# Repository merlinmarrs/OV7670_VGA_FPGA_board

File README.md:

# OV7670_VGA_FPGA_board

An iCE40HX4K Lattice FPGA development board which takes OV7670 camera-in at 30 frames per second and outputs 640x480 VGA @ 60Hz at a resolution of 320x120 in black and white. (The image above is a bit misleading, the OV7670 needs to be plugged in at the edge of the board next to the buttons, not in the center of the board)

The board can work stand-alone with a USB-C or it can be plugged-in to an Arduino to more easily change registers on the OV7670.

# Acknowledgements : 

The FPGA board design was inspired by the iCEstick Evaluation Kit and the [Alhambra] (https://alhambrabits.com/alhambra-2/) which was also an inspiration for the VGA output code.
Verilog code for the OV7670 inspired by the FPGA class 6.111 (Introductory Digital Systems Laboratory) [OV7670-Verilog](https://github.com/westonb/OV7670-Verilog). 
The first prototype of this board was supported by the [IFT](https://ift.devinci.fr/).

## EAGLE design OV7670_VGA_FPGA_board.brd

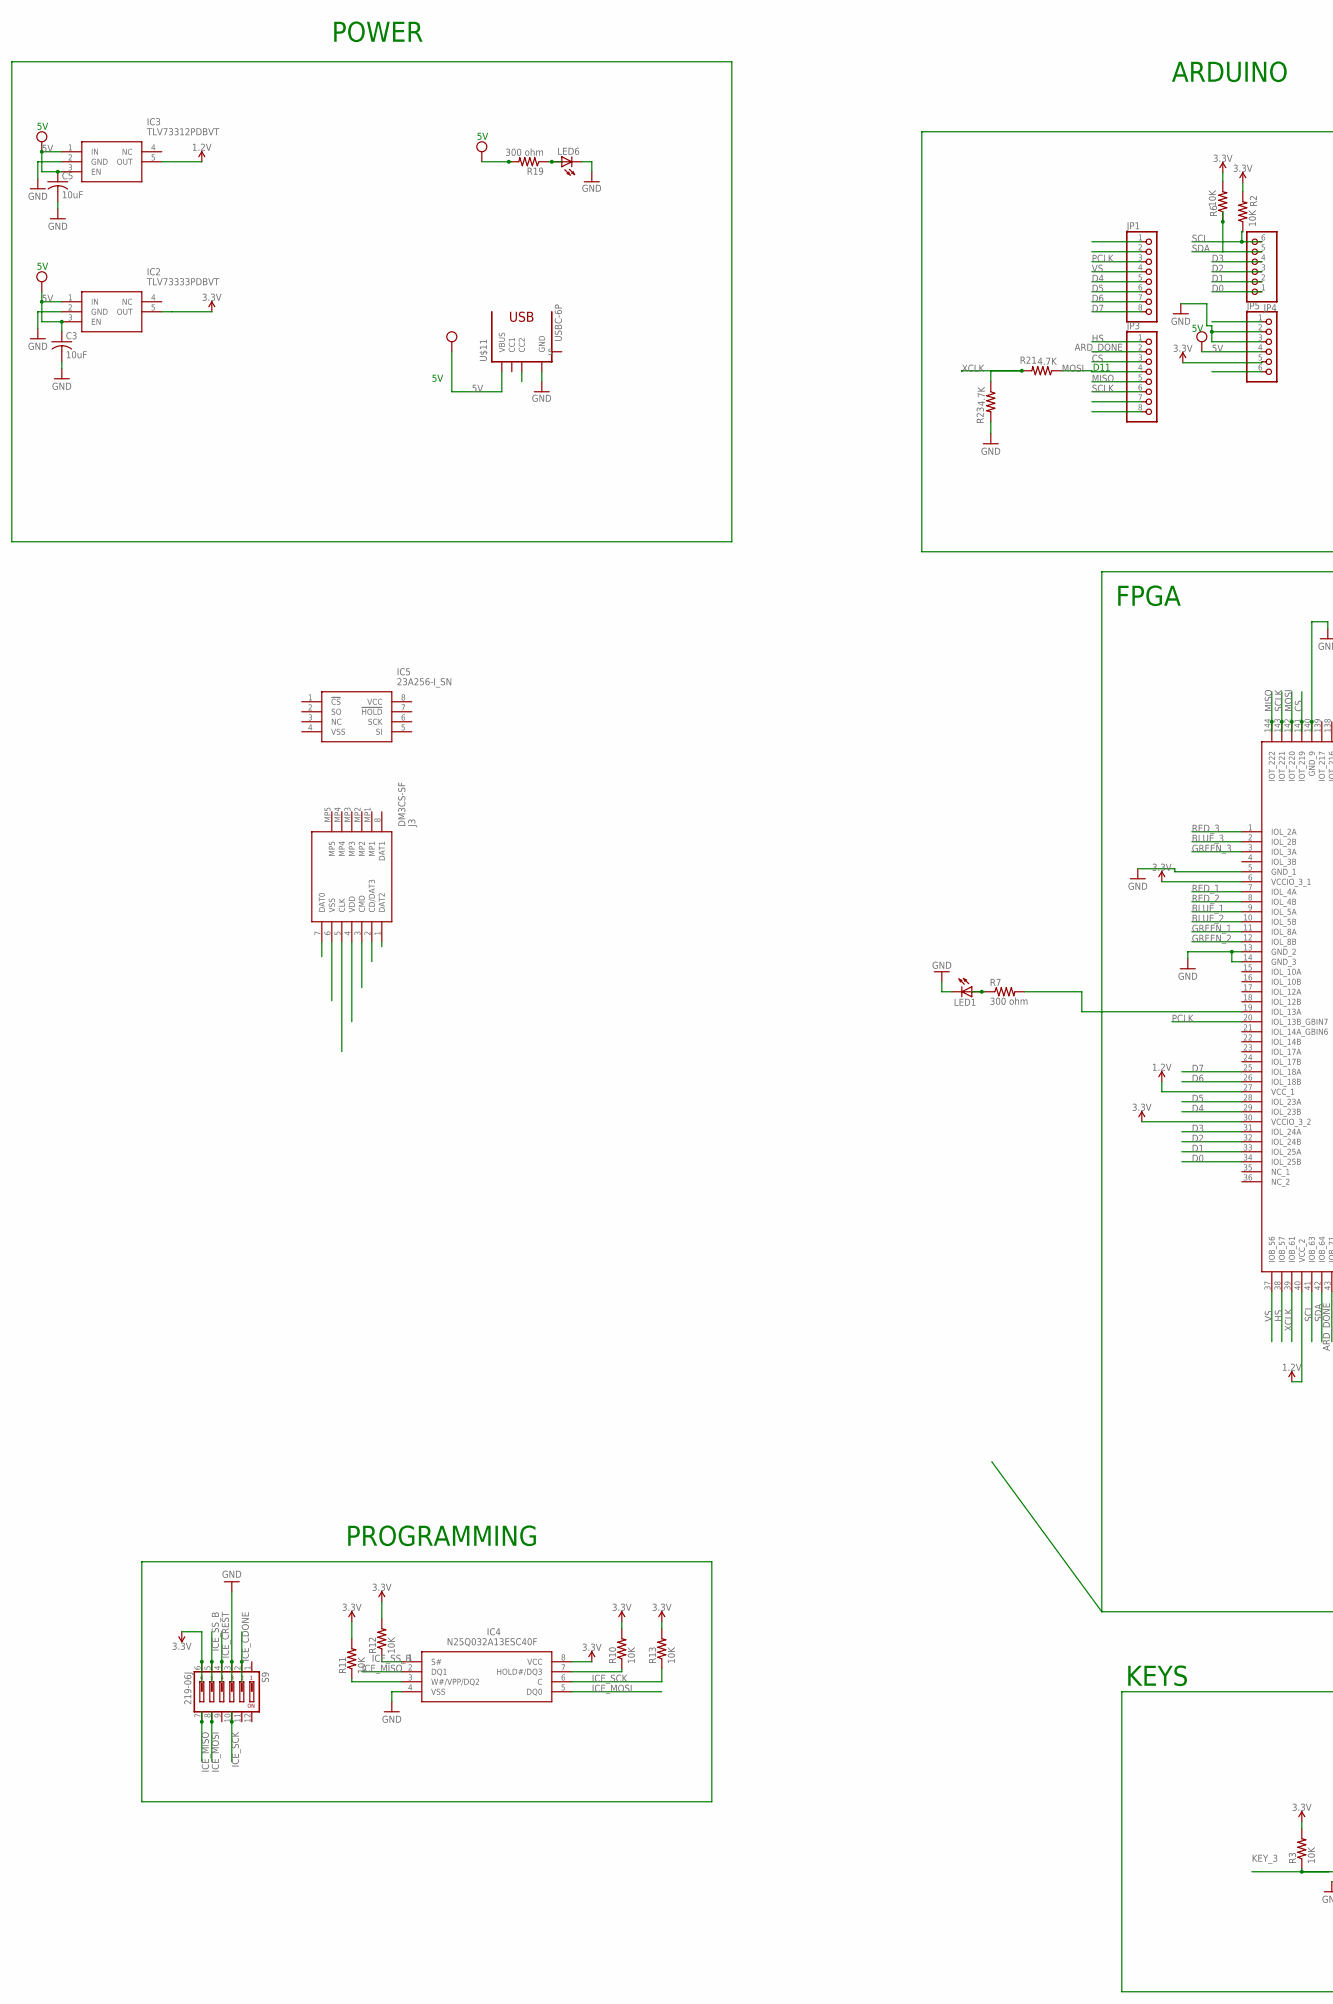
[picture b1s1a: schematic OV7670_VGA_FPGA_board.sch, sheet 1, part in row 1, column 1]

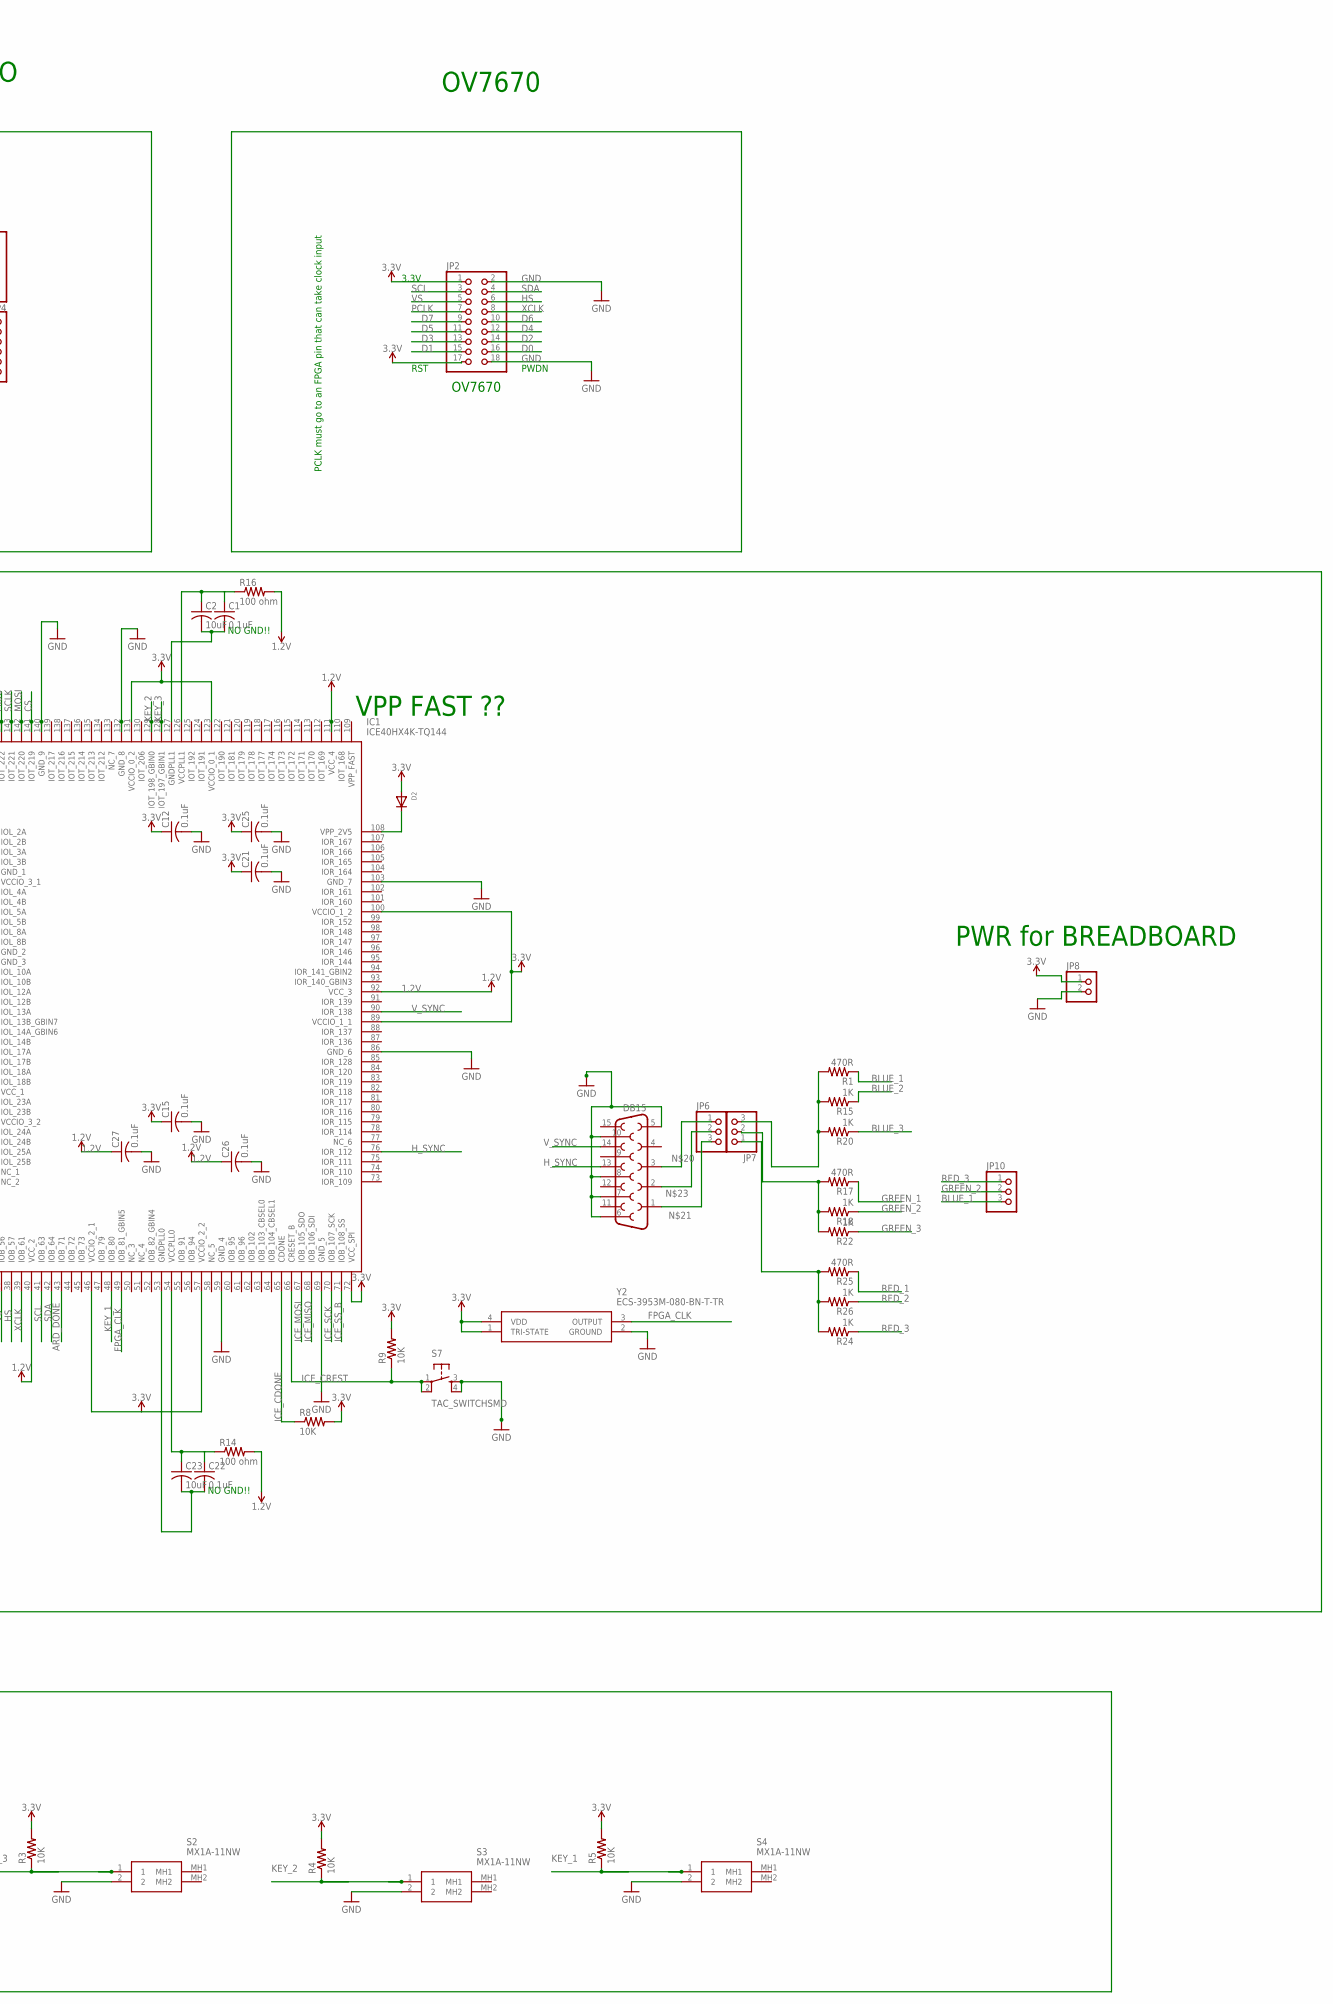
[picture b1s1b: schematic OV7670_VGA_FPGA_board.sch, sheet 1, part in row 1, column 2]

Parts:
C1, C12, C15, C21, C22, C25, C26, C27: 0.1uF; C0805
C2, C3, C5, C23: 10uF; C0805
D2: DIODESOD-323F; SOD-323F
IC1: ICE40HX4K-TQ144; QFP50P2200X2200X160-144N
IC2: TLV73333PDBVT; SOT95P280X145-5N
IC3: TLV73312PDBVT; SOT95P280X145-5N
IC4: N25Q032A13ESC40F; SOIC127P600X175-8N
IC5: 23A256-I_SN; SOIC127P600X175-8N
J3: DM3CS-SF; DM3CSSF
JP1, JP3: PINHD-1X8CLEANBIG; 1X08-CLEANBIG
JP2: PINHD-2X9/90; 2X09/90
JP4, JP5: PINHD-1X6CB; 1X06-CLEANBIG
JP6, JP7, JP10: PINHD-1X3; 1X03
JP8: PINHD-1X2; 1X02
LED1, LED6: LEDCHIPLED_0805; CHIPLED_0805
R1, R17, R25: 470R; R0805
R2, R3, R4, R5, R6, R8, R9, R10, R11, R12, R13: 10K; R0805
R7, R19: 300 ohm; R0805
R14, R16: 100 ohm; R0805
R15, R18, R20, R22, R24, R26: 1K; R0805
R21, R23: 4.7K; R0805
S2, S3, S4: MX1A-11NW; MX1A11NW
S7: TAC_SWITCHSMD; TACTILE-SWITCH-SMD
S9: 219-06J; CTS-219-06J
U$1: DB15
U$11: USBC-6P; USCX-06FX-XXMX-01
Y2: ECS-3953M-080-BN-T-TR; ECS3953M080BNTTR

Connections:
1.2V: C26.1, C27.1, IC1.27 (VCC_1), IC1.40 (VCC_2), IC1.92 (VCC_3), IC1.111 (VCC_4), IC3.5 (OUT), R14.2, R16.2
3.3V: C12.1, C15.1, C21.1, C25.1, D2.A, IC1.6 (VCCIO_3_1), IC1.30 (VCCIO_3_2), IC1.46 (VCCIO_2_1), IC1.57 (VCCIO_2_2), IC1.72 (VCC_SPI), IC1.89 (VCCIO_1_1), IC1.100 (VCCIO_1_2), IC1.123 (VCCIO_0_1), IC1.131 (VCCIO_0_2), IC2.5 (OUT), IC4.8 (VCC), JP2.1, JP2.17, JP5.5, JP8.1, R2.2, R3.2, R4.2, R5.2, R6.2, R8.2, R9.2, R10.2, R11.2, R12.2, R13.2, S9.6, Y2.1 (TRI-STATE), Y2.4 (VDD)
3.3V1: J3.4 (VDD)
5V: C3.1, C5.1, IC2.1 (IN), IC2.3 (EN), IC3.1 (IN), IC3.3 (EN), JP5.4, R19.2, U$11.VBUS1 (VBUS), U$11.VBUS2 (VBUS)
ARD_DONE: IC1.43 (IOB_71), JP3.2
BLUE: JP7.3, R1.2, R15.2, R20.2
BLUE_1: IC1.9 (IOL_5A), JP10.3, R1.1
BLUE_2: IC1.10 (IOL_5B), R15.1
BLUE_3: IC1.2 (IOL_2B), R20.1
CMD: J3.3 (CMD)
CS: IC1.141 (IOT_219), JP3.3
D0: IC1.34 (IOL_25B), JP2.16, JP4.1
D1: IC1.33 (IOL_25A), JP2.15, JP4.2
D2: IC1.32 (IOL_24B), JP2.14, JP4.3
D3: IC1.31 (IOL_24A), JP2.13, JP4.4
D4: IC1.29 (IOL_23B), JP1.5, JP2.12
D5: IC1.28 (IOL_23A), JP1.6, JP2.11
D6: IC1.26 (IOL_18B), JP1.7, JP2.10
D7: IC1.25 (IOL_18A), JP1.8, JP2.9
DAT0: J3.7 (DAT0)
DAT2: J3.1 (DAT2)
DAT3: J3.2 (CD/DAT3)
FPGA_CLK: IC1.49 (IOB_81_GBIN5), Y2.3 (OUTPUT)
GND: C3.2, C5.2, C12.2, C15.2, C21.2, C25.2, C26.2, C27.2, IC1.5 (GND_1), IC1.13 (GND_2), IC1.14 (GND_3), IC1.59 (GND_4), IC1.69 (GND_5), IC1.86 (GND_6), IC1.103 (GND_7), IC1.132 (GND_8), IC1.140 (GND_9), IC2.2 (GND), IC3.2 (GND), IC4.4 (VSS), JP2.2, JP2.18, JP5.2, JP5.3, JP8.2, LED1.C, LED6.C, R23.2, S2.2, S3.2, S4.2, S7.3, S7.4, S9.3, U$1.5, U$1.6, U$1.7, U$1.8, U$1.10, U$11.GND1 (GND), U$11.GND2 (GND), Y2.2 (GROUND)
GND1: J3.6 (VSS)
GREEN: JP7.2, R17.2, R18.2, R22.2
GREEN_1: IC1.11 (IOL_8A), R17.1
GREEN_2: IC1.12 (IOL_8B), JP10.2, R18.1
GREEN_3: IC1.3 (IOL_3A), R22.1
HS: IC1.38 (IOB_57), JP2.6, JP3.1
H_SYNC: IC1.76 (IOR_112), U$1.13
ICE_CDONE: IC1.65 (CDONE), R8.1, S9.2
ICE_CREST: IC1.66 (CRESET_B), R9.1, S7.1, S7.2, S9.4
ICE_MISO: IC1.68 (IOB_106_SDI), IC4.2 (DQ1), S9.7
ICE_MOSI: IC1.67 (IOB_105_SDO), IC4.5 (DQ0), S9.8
ICE_SCK: IC1.70 (IOB_107_SCK), IC4.6 (C), R13.1, S9.10
ICE_SS_B: IC1.71 (IOB_108_SS), IC4.1 (S#), R12.1, S9.5
KEY_1: IC1.48 (IOB_80), R5.1, S4.1
KEY_2: IC1.129 (IOT_198_GBIN0), R4.1, S3.1
KEY_3: IC1.128 (IOT_197_GBIN1), R3.1, S2.1
MISO: IC1.144 (IOT_222), JP3.5
MOSI: IC1.142 (IOT_220), JP3.4, R21.1
unnamed: IC4.7 (HOLD#/DQ3), R10.1
unnamed: LED6.A, R19.1
unnamed: IC4.3 (W#/VPP/DQ2), R11.1
unnamed: C22.1, C23.1, IC1.54 (VCCPLL0), R14.1
unnamed: LED1.A, R7.1
unnamed: IC1.19 (IOL_13A), R7.2
unnamed: D2.C, IC1.108 (VPP_2V5)
unnamed: JP6.1, U$1.3
unnamed: JP6.3, U$1.1
unnamed: C1.1, C2.1, IC1.126 (VCCPLL1), R16.1
unnamed: JP6.2, U$1.2
unnamed: C1.2, C2.2, IC1.127 (GNDPLL1)
unnamed: C22.2, C23.2, IC1.53 (GNDPLL0)
PCLK: IC1.20 (IOL_13B_GBIN7), JP1.3, JP2.7
RED: JP7.1, R24.2, R25.2, R26.2
RED_1: IC1.7 (IOL_4A), R25.1
RED_2: IC1.8 (IOL_4B), R26.1
RED_3: IC1.1 (IOL_2A), JP10.1, R24.1
SCL: IC1.41 (IOB_63), JP2.3, JP4.6, R2.1
SCLK: IC1.143 (IOT_221), JP3.6
SDA: IC1.42 (IOB_64), JP2.4, JP4.5, R6.1
SD_CLK: J3.5 (CLK)
VS: IC1.37 (IOB_56), JP1.4, JP2.5
V_SYNC: IC1.90 (IOR_138), U$1.14
XCLK: IC1.39 (IOB_61), JP2.8, R21.2, R23.1

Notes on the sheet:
NO GND!!
POWER
PROGRAMMING
FPGA
OV7670
ARDUINO
PCLK must go to an FPGA pin that can take clock input
KEYS
RST
D11
PWDN
3.3V
PWR for BREADBOARD
VPP FAST ??

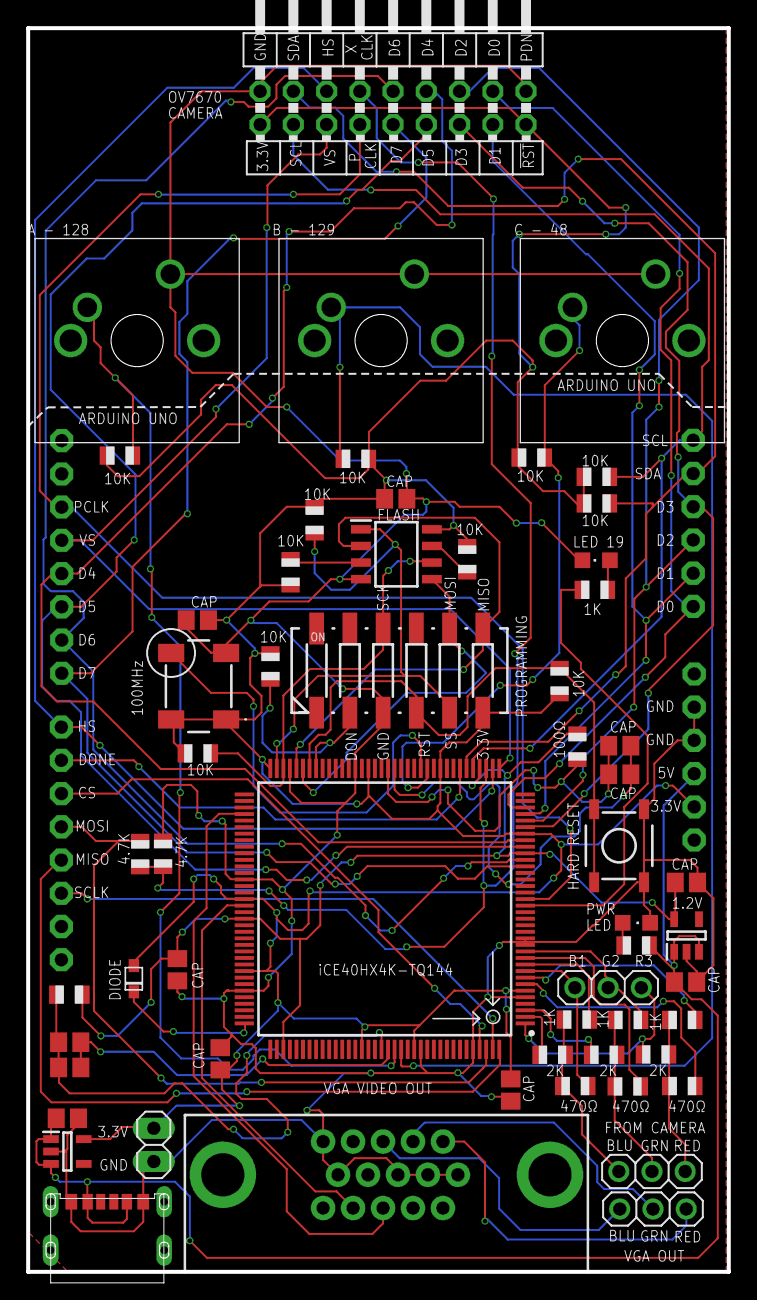
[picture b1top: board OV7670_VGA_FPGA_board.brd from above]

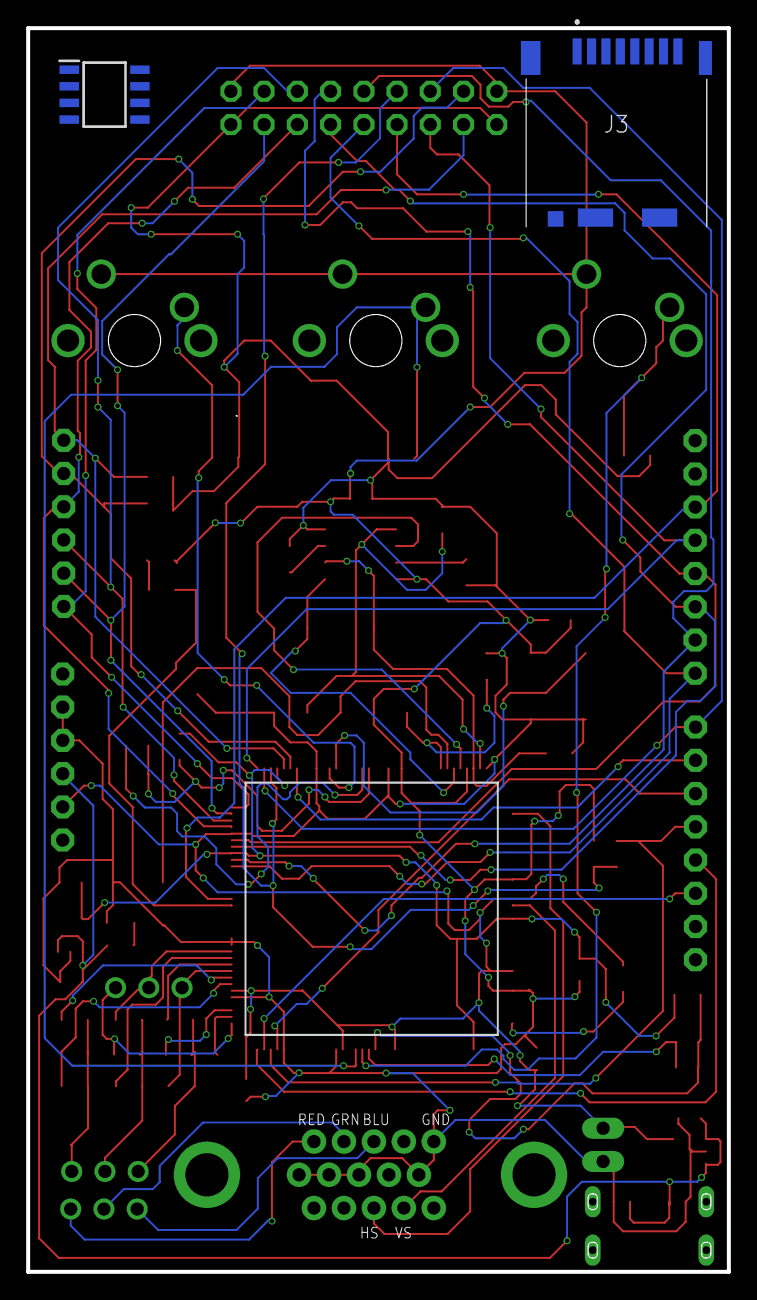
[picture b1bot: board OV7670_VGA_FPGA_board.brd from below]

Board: 2 copper layers, 53.5 x 95.0 mm, 64 parts (2 on the bottom side), 60 nets.

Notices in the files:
parts and their libraries:
SparkFun-Retired: Licensing: Creative Commons ShareAlike 4.0 International - https://creativecommons.org/licenses/by-sa/4.0
